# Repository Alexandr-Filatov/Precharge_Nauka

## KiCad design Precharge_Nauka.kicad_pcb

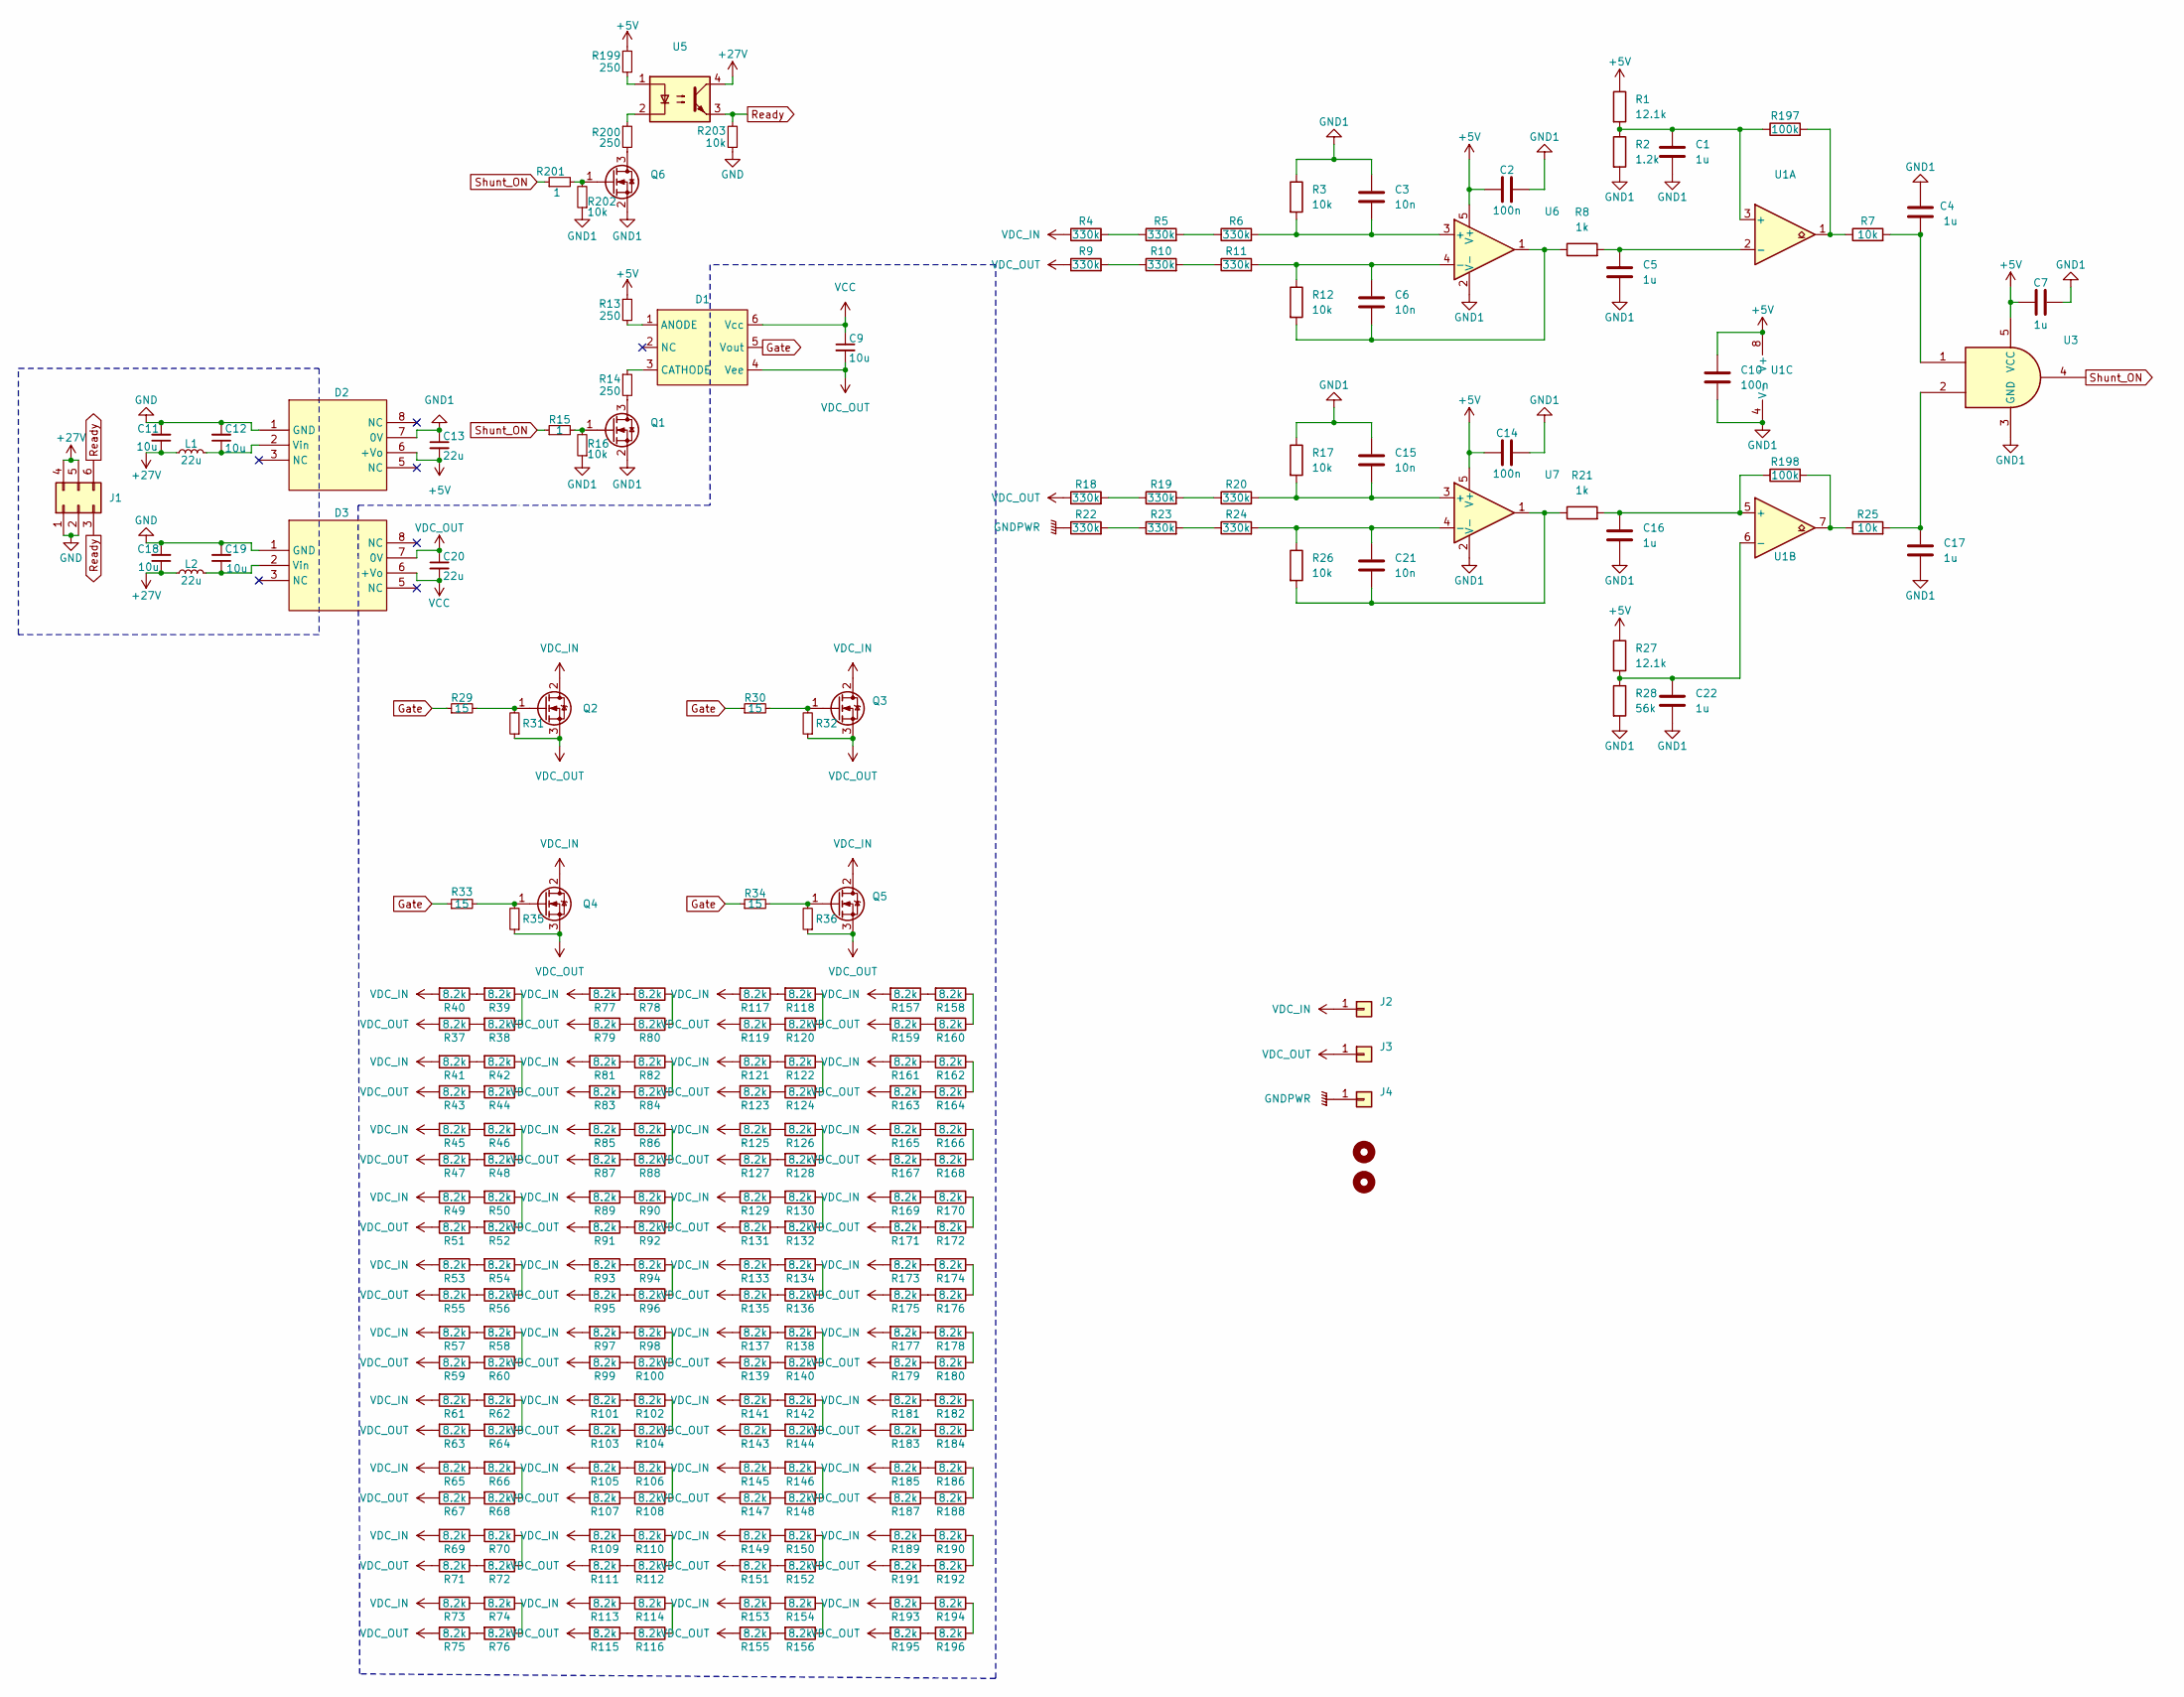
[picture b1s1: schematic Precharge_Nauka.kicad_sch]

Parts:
C1, C4, C5, C7, C16, C17, C22: 1u; C_0805_2012Metric_Pad1.18x1.45mm_HandSolder
C2, C10, C14: 100n; C_0805_2012Metric_Pad1.18x1.45mm_HandSolder
C3, C6, C15, C21: 10n; C_0805_2012Metric_Pad1.18x1.45mm_HandSolder
C9, C11, C12, C18, C19: 10u; C_1206_3216Metric_Pad1.33x1.80mm_HandSolder
C13, C20: 22u; C_1206_3216Metric_Pad1.33x1.80mm_HandSolder
D1: SOW6
D2, D3: UWF_S-3WR3
H1, H2: MountingHole_4.3mm_M4
J1: Molex_Micro-Fit_3.0_43045-0612_2x03_P3.00mm_Vertical
J2, J3: SMD_15mm
J4: SMD_8mm
L1, L2: 22u; L_1812_4532Metric_Pad1.30x3.40mm_HandSolder
Q1, Q6: SOT-23
Q2, Q3, Q4, Q5: TO-247-3_Horizontal_TabUp
R1, R27: 12.1k; R_0805_2012Metric_Pad1.20x1.40mm_HandSolder
R2: 1.2k; R_0805_2012Metric_Pad1.20x1.40mm_HandSolder
R3, R7, R12, R16, R17, R25, R26, R31, R32, R35, R36, R202, R203: 10k; R_0805_2012Metric_Pad1.20x1.40mm_HandSolder
R4, R5, R6, R9, R10, R11, R18, R19, R20, R22, R23, R24: 330k; R_1206_3216Metric
R8, R21: 1k; R_0805_2012Metric_Pad1.20x1.40mm_HandSolder
R13, R14, R199, R200: 250; R_0805_2012Metric_Pad1.20x1.40mm_HandSolder
R15, R201: 1; R_0805_2012Metric_Pad1.20x1.40mm_HandSolder
R28: 56k; R_0805_2012Metric_Pad1.20x1.40mm_HandSolder
R29, R30, R33, R34: 15; R_1206_3216Metric_Pad1.30x1.75mm_HandSolder
R37, R38, R39, R40, R41, R42, R43, R44, R45, R46, R47, R48, R49, R50, R51, R52, R53, R54, R55, R56, R57, R58, R59, R60, R61, R62, R63, R64, R65, R66, R67, R68, R69, R70, R71, R72, R73, R74, R75, R76, R77, R78, R79, R80, R81, R82, R83, R84, R85, R86, R87, R88, R89, R90, R91, R92, R93, R94, R95, R96, R97, R98, R99, R100, R101, R102, R103, R104, R105, R106, R107, R108, R109, R110, R111, R112, R113, R114, R115, R116, R117, R118, R119, R120, R121, R122, R123, R124, R125, R126, R127, R128, R129, R130, R131, R132, R133, R134, R135, R136, R137, R138, R139, R140, R141, R142, R143, R144, R145, R146, R147, R148, R149, R150, R151, R152, R153, R154, R155, R156, R157, R158, R159, R160, R161, R162, R163, R164, R165, R166, R167, R168, R169, R170, R171, R172, R173, R174, R175, R176, R177, R178, R179, R180, R181, R182, R183, R184, R185, R186, R187, R188, R189, R190, R191, R192, R193, R194, R195, R196: 8.2k; R_2512_6332Metric_Pad1.40x3.35mm_HandSolder
R197, R198: 100k; R_0805_2012Metric_Pad1.20x1.40mm_HandSolder
U1: SOP-8_3.76x4.96mm_P1.27mm
U3: SOT-23-5_HandSoldering
U5: DIP-4_W7.62mm
U6, U7: SOT-23-5

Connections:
+5V: C2.1, C7.1, C10.2, C13.2, C14.1, D2.6 (+Vo), R1.1, R13.1, R27.1, R199.1, U1.8 (V+), U3.5 (VCC), U6.5 (V+), U7.5 (V+)
+27V: C11.1, C18.1, J1.4, J1.5, L1.2, L2.2, U5.4
GND: C11.2, C12.2, C18.2, C19.2, D2.1 (GND), D3.1 (GND), J1.1, J1.2, R203.1
GND1: C1.2, C2.2, C3.1, C4.2, C5.2, C7.2, C10.1, C13.1, C14.2, C15.1, C16.2, C17.2, C22.2, D2.7 (0V), Q1.2 (S), Q6.2 (S), R2.2, R3.1, R16.1, R17.1, R28.2, R202.1, U1.4 (V-), U3.3 (GND), U6.2 (V-), U7.2 (V-)
GNDPWR: J4.1 (Pin_1_1), R22.1
Gate: D1.5 (Vout), R29.1, R30.1, R33.1, R34.1
unnamed: C4.1, R7.2, U3.1
unnamed: C6.2, R8.1, R12.2, U6.1
unnamed: C17.1, R25.2, U3.2
unnamed: C21.2, R21.1, R26.2, U7.1
unnamed: D1.1 (ANODE), R13.2
unnamed: D1.3 (CATHODE), R14.1
unnamed: C12.1, D2.2 (Vin), L1.1
unnamed: C19.1, D3.2 (Vin), L2.1
unnamed: Q1.3 (D), R14.2
unnamed: Q1.1 (G), R15.2, R16.2
unnamed: Q2.1 (G), R29.2, R31.2
unnamed: Q3.1 (G), R30.2, R32.2
unnamed: Q4.1 (G), R33.2, R35.2
unnamed: Q5.1 (G), R34.2, R36.2
unnamed: Q6.3 (D), R200.2
unnamed: Q6.1 (G), R201.2, R202.2
unnamed: R4.2, R5.1
unnamed: R5.2, R6.1
unnamed: R9.2, R10.1
unnamed: R10.2, R11.1
unnamed: R18.2, R19.1
unnamed: R19.2, R20.1
unnamed: R22.2, R23.1
unnamed: R23.2, R24.1
unnamed: R37.1, R38.2
unnamed: R38.1, R39.1
unnamed: R39.2, R40.1
unnamed: R41.1, R42.2
unnamed: R42.1, R44.1
unnamed: R43.1, R44.2
unnamed: R45.1, R46.2
unnamed: R46.1, R48.1
unnamed: R47.1, R48.2
unnamed: R49.1, R50.2
unnamed: R50.1, R52.1
unnamed: R51.1, R52.2
unnamed: R53.1, R54.2
unnamed: R54.1, R56.1
unnamed: R55.1, R56.2
unnamed: R57.1, R58.2
unnamed: R58.1, R60.1
unnamed: R59.1, R60.2
unnamed: R61.1, R62.2
unnamed: R62.1, R64.1
unnamed: R63.1, R64.2
unnamed: R65.1, R66.2
unnamed: R66.1, R68.1
unnamed: R67.1, R68.2
unnamed: R69.1, R70.2
unnamed: R70.1, R72.1
unnamed: R71.1, R72.2
unnamed: R73.1, R74.2
unnamed: R74.1, R76.1
unnamed: R75.1, R76.2
unnamed: R77.1, R78.2
unnamed: R78.1, R80.1
unnamed: R79.1, R80.2
unnamed: R81.1, R82.2
unnamed: R82.1, R84.1
unnamed: R83.1, R84.2
unnamed: R85.1, R86.2
unnamed: R86.1, R88.1
unnamed: R87.1, R88.2
unnamed: R89.1, R90.2
unnamed: R90.1, R92.1
unnamed: R91.1, R92.2
unnamed: R93.1, R94.2
unnamed: R94.1, R96.1
unnamed: R95.1, R96.2
unnamed: R97.1, R98.2
unnamed: R98.1, R100.1
unnamed: R99.1, R100.2
unnamed: R101.1, R102.2
unnamed: R102.1, R104.1
unnamed: R103.1, R104.2
unnamed: R105.1, R106.2
unnamed: R106.1, R108.1
unnamed: R107.1, R108.2
unnamed: R109.1, R110.2
unnamed: R110.1, R112.1
unnamed: R111.1, R112.2
unnamed: R113.1, R114.2
unnamed: R114.1, R116.1
unnamed: R115.1, R116.2
unnamed: R117.1, R118.2
unnamed: R118.1, R120.1
unnamed: R119.1, R120.2
unnamed: R121.1, R122.2
unnamed: R122.1, R124.1
unnamed: R123.1, R124.2
unnamed: R125.1, R126.2
unnamed: R126.1, R128.1
unnamed: R127.1, R128.2
unnamed: R129.1, R130.2
unnamed: R130.1, R132.1
unnamed: R131.1, R132.2
unnamed: R133.1, R134.2
unnamed: R134.1, R136.1
unnamed: R135.1, R136.2
unnamed: R137.1, R138.2
unnamed: R138.1, R140.1
unnamed: R139.1, R140.2
unnamed: R141.1, R142.2
unnamed: R142.1, R144.1
unnamed: R143.1, R144.2
unnamed: R145.1, R146.2
unnamed: R146.1, R148.1
unnamed: R147.1, R148.2
unnamed: R149.1, R150.2
unnamed: R150.1, R152.1
unnamed: R151.1, R152.2
unnamed: R153.1, R154.2
unnamed: R154.1, R156.1
unnamed: R155.1, R156.2
unnamed: R157.1, R158.2
unnamed: R158.1, R160.1
unnamed: R159.1, R160.2
unnamed: R161.1, R162.2
unnamed: R162.1, R164.1
unnamed: R163.1, R164.2
unnamed: R165.1, R166.2
unnamed: R166.1, R168.1
unnamed: R167.1, R168.2
unnamed: R169.1, R170.2
unnamed: R170.1, R172.1
unnamed: R171.1, R172.2
unnamed: R173.1, R174.2
unnamed: R174.1, R176.1
unnamed: R175.1, R176.2
unnamed: R177.1, R178.2
unnamed: R178.1, R180.1
unnamed: R179.1, R180.2
unnamed: R181.1, R182.2
unnamed: R182.1, R184.1
unnamed: R183.1, R184.2
unnamed: R185.1, R186.2
unnamed: R186.1, R188.1
unnamed: R187.1, R188.2
unnamed: R189.1, R190.2
unnamed: R190.1, R192.1
unnamed: R191.1, R192.2
unnamed: R193.1, R194.2
unnamed: R194.1, R196.1
unnamed: R195.1, R196.2
unnamed: R7.1, R197.2, U1.1
unnamed: R25.1, R198.2, U1.7
unnamed: R199.2, U5.1
unnamed: R200.1, U5.2
unnamed: C1.1, R1.2, R2.1, R197.1, U1.3 (+)
unnamed: C5.1, R8.2, U1.2 (-)
unnamed: C16.1, R21.2, R198.1, U1.5 (+)
unnamed: C22.1, R27.2, R28.1, U1.6 (-)
unnamed: C3.2, R3.2, R6.2, U6.3 (+)
unnamed: C6.1, R11.2, R12.1, U6.4 (-)
unnamed: C15.2, R17.2, R20.2, U7.3 (+)
unnamed: C21.1, R24.2, R26.1, U7.4 (-)
Ready: J1.3, J1.6, R203.2, U5.3
Shunt_ON: R15.1, R201.1, U3.4
VCC: C9.1, C20.2, D1.6 (Vcc), D3.6 (+Vo)
VDC_IN: J2.1 (Pin_1_1), Q2.2 (D), Q3.2 (D), Q4.2 (D), Q5.2 (D), R4.1, R40.2, R41.2, R45.2, R49.2, R53.2, R57.2, R61.2, R65.2, R69.2, R73.2, R77.2, R81.2, R85.2, R89.2, R93.2, R97.2, R101.2, R105.2, R109.2, R113.2, R117.2, R121.2, R125.2, R129.2, R133.2, R137.2, R141.2, R145.2, R149.2, R153.2, R157.2, R161.2, R165.2, R169.2, R173.2, R177.2, R181.2, R185.2, R189.2, R193.2
VDC_OUT: C9.2, C20.1, D1.4 (Vee), D3.7 (0V), J3.1 (Pin_1_1), Q2.3 (S), Q3.3 (S), Q4.3 (S), Q5.3 (S), R9.1, R18.1, R31.1, R32.1, R35.1, R36.1, R37.2, R43.2, R47.2, R51.2, R55.2, R59.2, R63.2, R67.2, R71.2, R75.2, R79.2, R83.2, R87.2, R91.2, R95.2, R99.2, R103.2, R107.2, R111.2, R115.2, R119.2, R123.2, R127.2, R131.2, R135.2, R139.2, R143.2, R147.2, R151.2, R155.2, R159.2, R163.2, R167.2, R171.2, R175.2, R179.2, R183.2, R187.2, R191.2, R195.2

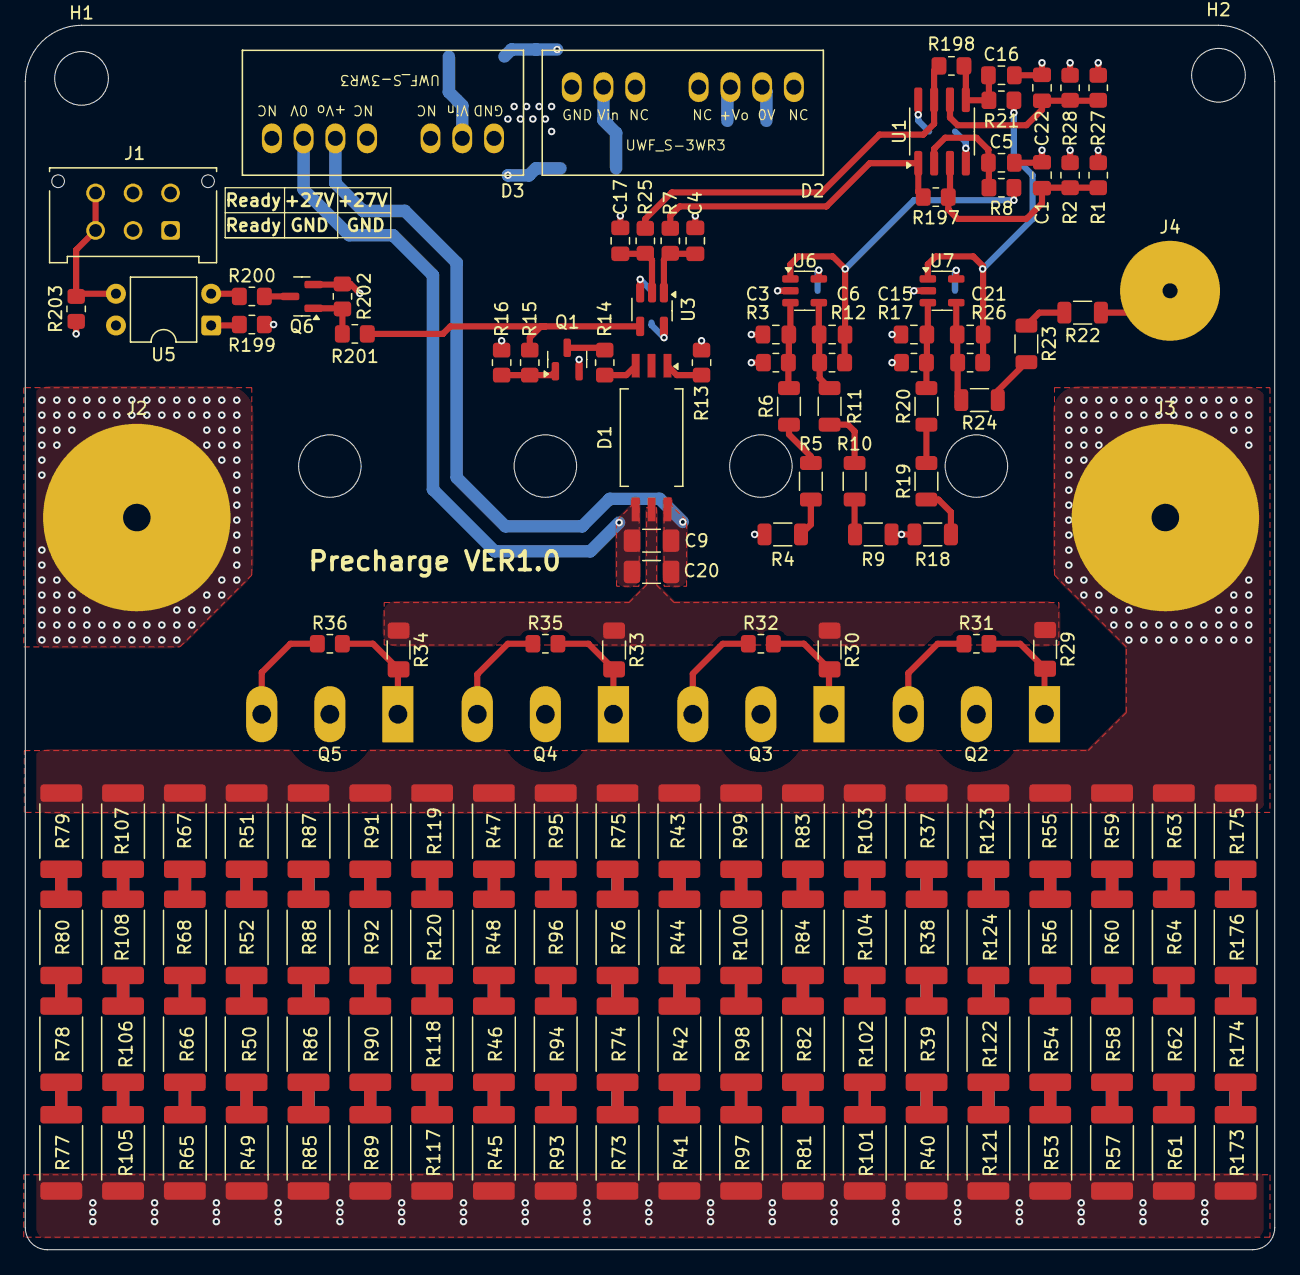
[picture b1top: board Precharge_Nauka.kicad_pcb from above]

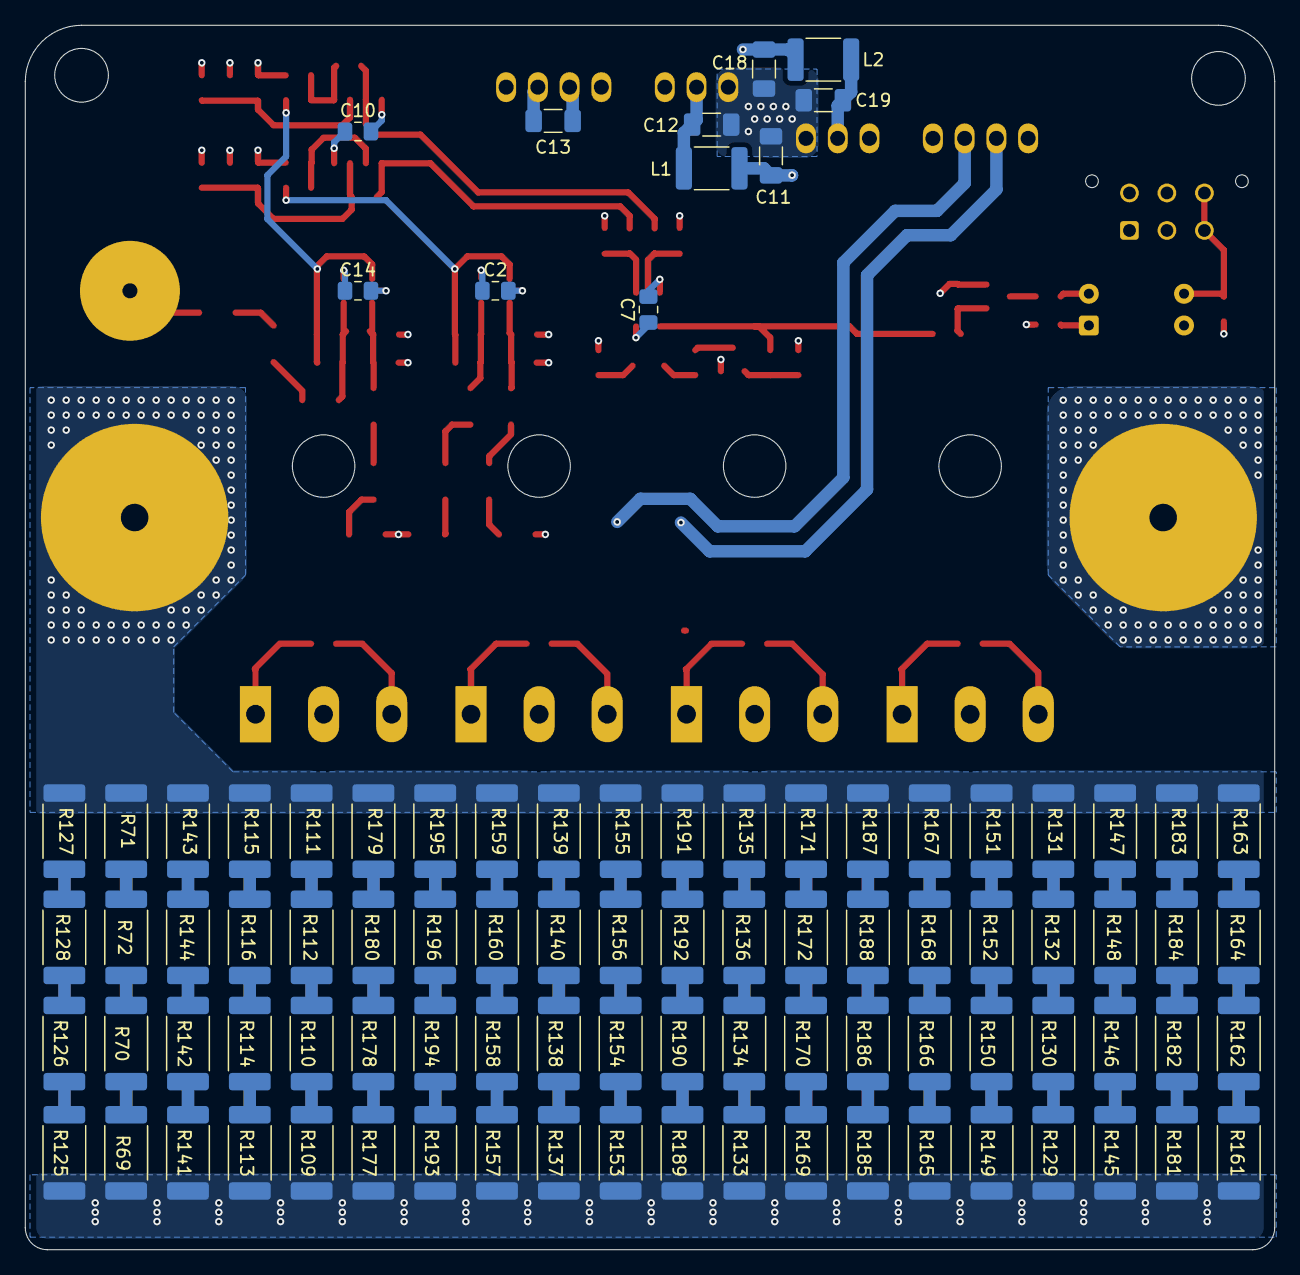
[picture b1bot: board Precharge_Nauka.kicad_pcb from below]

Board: 4 copper layers, 100.0 x 98.0 mm, 246 parts (91 on the bottom side), 167 nets.

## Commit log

2025-12-25 zero commit
2025-12-26 VER1.0: закончил основную схему и раскидал на плате
2025-12-29 VER1.0: заменил цементные на 2512 резисторы
2026-03-03 VER1.0: надо проверить посадку новых транзисторов. Добавил обратную свзязь для компараторов
2026-03-16 VER1.0: добавил силовые стойки и развел силу
2026-03-17 VER1.0: увеличил фильтры компаратора, изменил схему предзарядных резисторов
2026-03-18 VER1.0: изменил контур платы, сложно скомпоновать в размер
2026-04-09 VER1.0: уместил в прямоугольник все, заменил операционники измерительные
2026-06-09 VER1.0: подготовил файлы для производства v1.0
